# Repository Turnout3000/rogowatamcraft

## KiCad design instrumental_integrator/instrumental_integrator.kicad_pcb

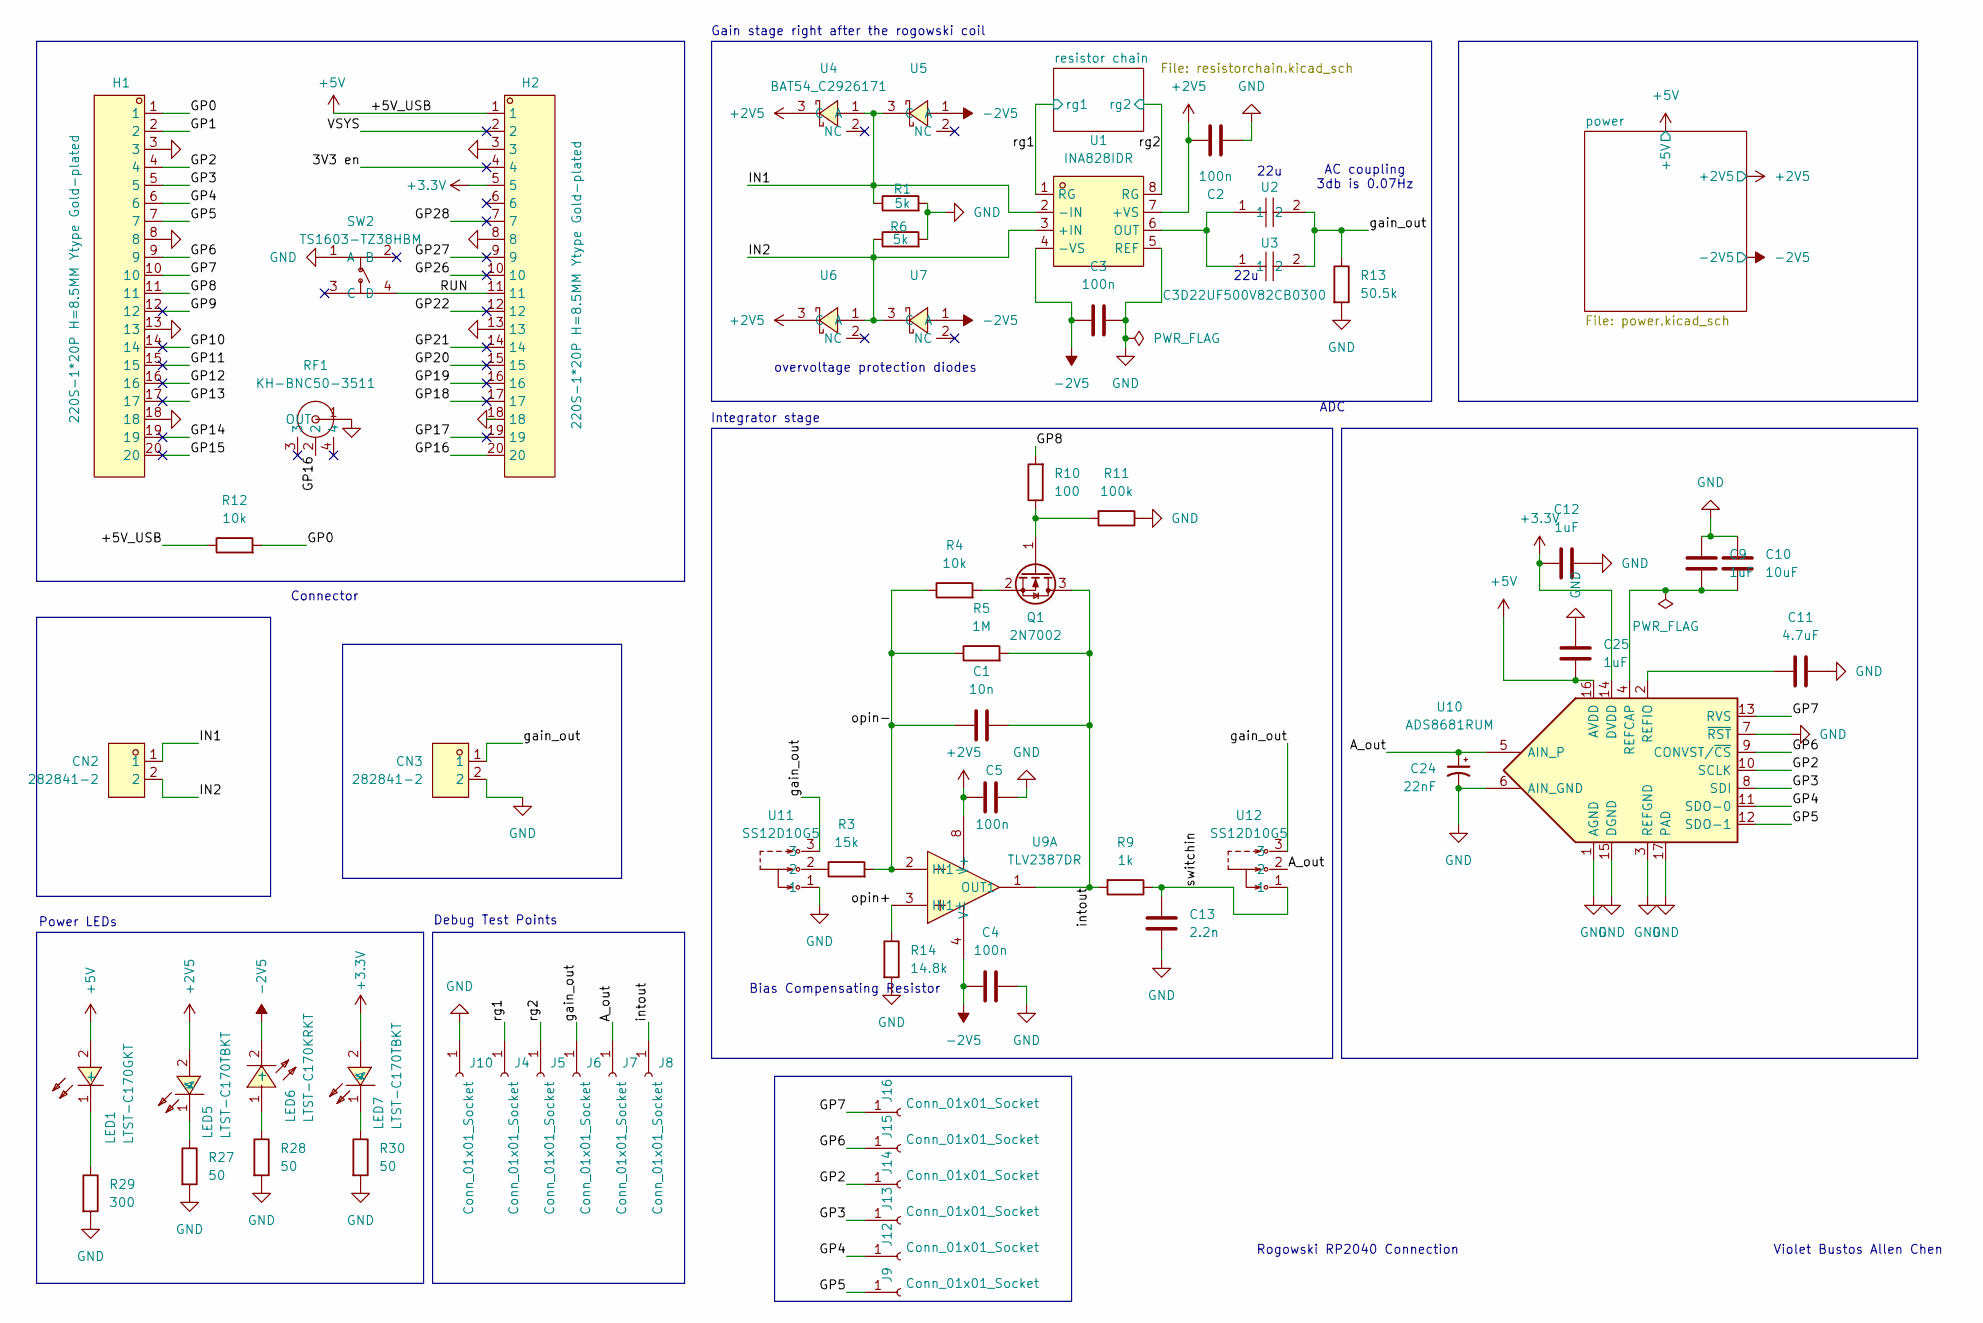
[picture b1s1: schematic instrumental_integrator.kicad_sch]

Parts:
C1: 10n; C_0603_1608Metric
C2, C3, C4, C5: 100n; C_0805_2012Metric
C9, C12, C25: 1uF; C_0603_1608Metric
C10: 10uF; C_0805_2012Metric
C11: 4.7uF; C_0805_2012Metric
C13: 2.2n; C_0805_2012Metric
C24: 22nF; C_1206_3216Metric
CN2, CN3: 282841-2; CONN-TH_2P-P5.08_282841-2; MPN 282841-2; LCSC Part C589673
H1, H2: 220S-1*20P H=8.5MM Ytype Gold-plated; HDR-TH_20P-P2.54-V-F; MPN B-2200S20P-A120; LCSC Part C124410
J4, J5, J6, J7, J8, J9, J10, J12, J13, J14, J15, J16: Conn_01x01_Socket; TestPoint_THTPad_1.0x1.0mm_Drill0.5mm
LED1: LTST-C170GKT; LED0805-RD_GREEN; MPN LTST-C170GKT; LCSC Part C125090
LED5, LED7: LTST-C170TBKT; LED0805-RD_BLUE; MPN LTST-C170TBKT; LCSC Part C98222
LED6: LTST-C170KRKT; LED0805-R-RD; MPN LTST-C170KRKT; LCSC Part C94868
Q1: 2N7002; SOT-23
R1, R6: 5k; R_0805_2012Metric
R3: 15k; R_0805_2012Metric
R4, R12: 10k; R_0805_2012Metric
R5: 1M; R_0805_2012Metric
R9: 1k; R_0805_2012Metric
R10: 100; R_0805_2012Metric
R11: 100k; R_0805_2012Metric
R13: 50.5k; R_0805_2012Metric
R14: 14.8k; R_0805_2012Metric
R27, R28, R30: 50; R_0805_2012Metric
R29: 300; R_0805_2012Metric
RF1: KH-BNC50-3511; ANT-TH_KH-BNC50-3511; MPN KH-BNC50-3511; LCSC Part C2837587
SW2: TS1603-TZ38HBM; SW-SMD_4P-L4.5-W4.5-P3.00-LS6.8; MPN TS1603-TZ38HBM; LCSC Part C36938886
U1: INA828IDR; SOIC-8_L4.9-W3.9-P1.27-LS6.0-BL; MPN INA828IDR; LCSC Part C544342
U2, U3: C3D22UF500V82CB0300; CAP-TH_L32.0-W22.0-P27.50-D1.3; MPN C3D22UF500V82CB0300; LCSC Part C5263851
U4, U5, U6, U7: BAT54_C2926171; SOT-23-3_L2.9-W1.3-P0.95-LS2.4-BR; MPN BAT54; LCSC Part C2926171
U9: TLV2387DR; SOIC-8_L4.9-W3.9-P1.27-LS6.2-BL; MPN TLV2387DR; LCSC Part C22445452
U10: ADS8681RUM; QFN-16-1EP_4x4mm_P0.65mm_EP2.7x2.7mm
U11, U12: SS12D10G5; SW-TH_SHOU-HAN_SS12D10G4; MPN SS12D10G5; LCSC Part C7431054

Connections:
+2V5: C2.1, C5.1, LED5.2 (A), U1.7 (+VS), U4.3 (C), U6.3 (C), U9.8 (V+); also elsewhere on the board
+3.3V: C12.1, H2.5, LED7.2 (A), U10.14 (DVDD)
+5V: C25.1, H2.1, LED1.2 (+), R12.1, U10.16 (AVDD); also elsewhere on the board
-2V5: C3.2, C4.1, LED6.2 (-), U1.4 (-VS), U5.1 (A), U7.1 (A), U9.4 (V-); also elsewhere on the board
/3V3 en: H2.4
/A_out: C24.1, J7.1 (Pin_1_1), U10.5 (AIN_P), U12.2
/GP0: H1.1, R12.2
/GP1: H1.2
/GP2: H1.4, J14.1 (Pin_1_1), U10.10 (SCLK)
/GP3: H1.5, J13.1 (Pin_1_1), U10.8 (SDI)
/GP4: H1.6, J12.1 (Pin_1_1), U10.11 (SDO-0)
/GP5: H1.7, J9.1 (Pin_1_1), U10.12 (SDO-1)
/GP6: H1.9, J15.1 (Pin_1_1), U10.9 (CONVST/~CS)
/GP7: H1.10, J16.1 (Pin_1_1), U10.13 (RVS)
/GP8: H1.11, R10.2
/GP9: H1.12
/GP10: H1.14
/GP11: H1.15
/GP12: H1.16
/GP13: H1.17
/GP14: H1.19
/GP15: H1.20
/GP16: H2.20, RF1.2
/GP17: H2.19
/GP18: H2.17
/GP19: H2.16
/GP20: H2.15
/GP21: H2.14
/GP22: H2.12
/GP26: H2.10
/GP27: H2.9
/GP28: H2.7
/IN1: CN2.1, R1.1, U1.2 (-IN), U4.1 (A), U5.3 (C)
/IN2: CN2.2, R6.1, U1.3 (+IN), U6.1 (A), U7.3 (C)
/RUN: H2.11, SW2.4 (D)
/VSYS: H2.2
/gain_out: CN3.1, J6.1 (Pin_1_1), R13.1, U2.2, U3.2, U11.3, U12.3
/intout: C1.2, J8.1 (Pin_1_1), Q1.3 (D), R5.2, R9.2, U9.1 (OUT1)
/opin+: R14.1, U9.3 (IN1+)
/opin-: C1.1, R3.2, R4.1, R5.1, U9.2 (IN1-)
/rg1: J4.1 (Pin_1_1), U1.1 (RG); also elsewhere on the board
/rg2: J5.1 (Pin_1_1), U1.8 (RG); also elsewhere on the board
/switchin: C13.1, R9.1, U12.1
GND: C2.2, C3.1, C4.2, C5.2, C9.1, C10.1, C11.2, C12.2, C13.2, C24.2, C25.2, CN3.2, H1.3, H1.8, H1.13, H1.18, H2.3, H2.8, H2.13, H2.18, J10.1 (Pin_1_1), R1.2, R6.2, R11.1, R13.2, R14.2, R27.2, R28.2, R29.2, R30.2, RF1.1 (OUT), SW2.1 (A), U1.5 (REF), U10.1 (AGND), U10.3 (REFGND), U10.6 (AIN_GND), U10.7 (~RST), U10.15 (DGND), U10.17 (PAD), U11.1; also elsewhere on the board
unnamed: LED1.1 (-), R29.1
unnamed: LED5.1 (K), R27.1
unnamed: LED6.1 (+), R28.1
unnamed: LED7.1 (K), R30.1
unnamed: Q1.1 (G), R10.1, R11.2
unnamed: Q1.2 (S), R4.2
unnamed: R3.1, U11.2
unnamed: U1.6 (OUT), U2.1, U3.1
unnamed: C9.2, C10.2, U10.4 (REFCAP)
unnamed: C11.1, U10.2 (REFIO)

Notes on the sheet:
Gain stage right after the rogowski coil
Debug Test Points
ADC
Rogowski RP2040 Connection
22u
Power LEDs
Violet Bustos Allen Chen
Bias Compensating Resistor
AC coupling 3db is 0.07Hz
overvoltage protection diodes
Connector
Integrator stage

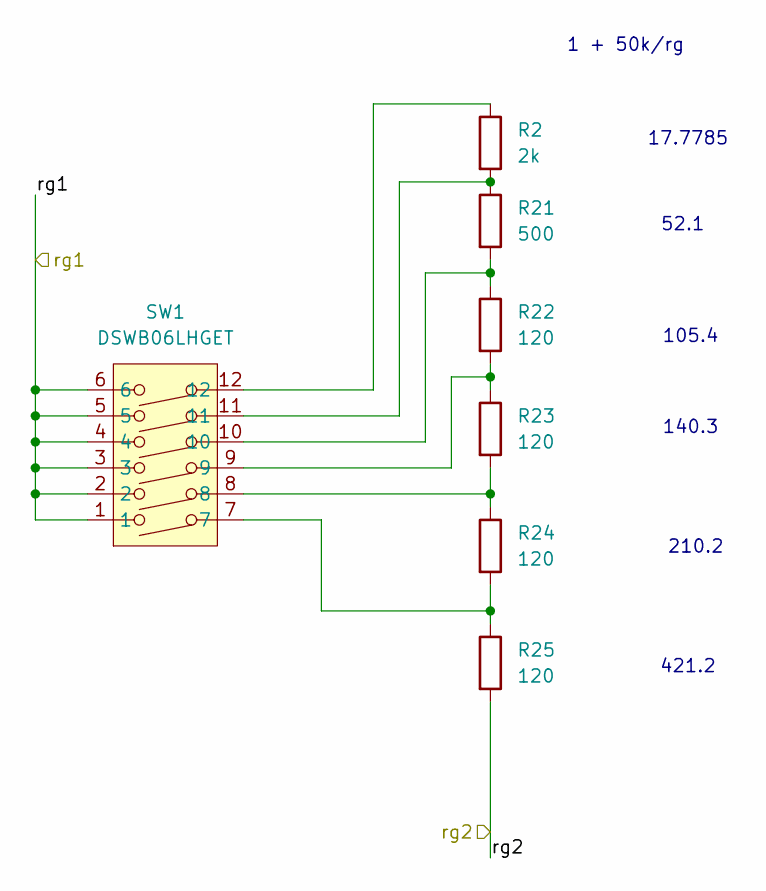
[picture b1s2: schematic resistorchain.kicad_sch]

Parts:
R2: 2k; R_0805_2012Metric
R21: 500; R_0805_2012Metric
R22, R23, R24, R25: 120; R_0805_2012Metric
SW1: DSWB06LHGET; SW-TH_DSWB06LHGET; MPN DSWB06LHGET; LCSC Part C99416

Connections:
/rg1: SW1.1, SW1.2, SW1.3, SW1.4, SW1.5, SW1.6; also elsewhere on the board
/rg2: R25.2; also elsewhere on the board
unnamed: R2.1, SW1.12
unnamed: R2.2, R21.1, SW1.11
unnamed: R21.2, R22.1, SW1.10
unnamed: R22.2, R23.1, SW1.9
unnamed: R23.2, R24.1, SW1.8
unnamed: R24.2, R25.1, SW1.7

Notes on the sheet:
1 + 50k/rg
140.3
210.2
17.7785
421.2
105.4
52.1

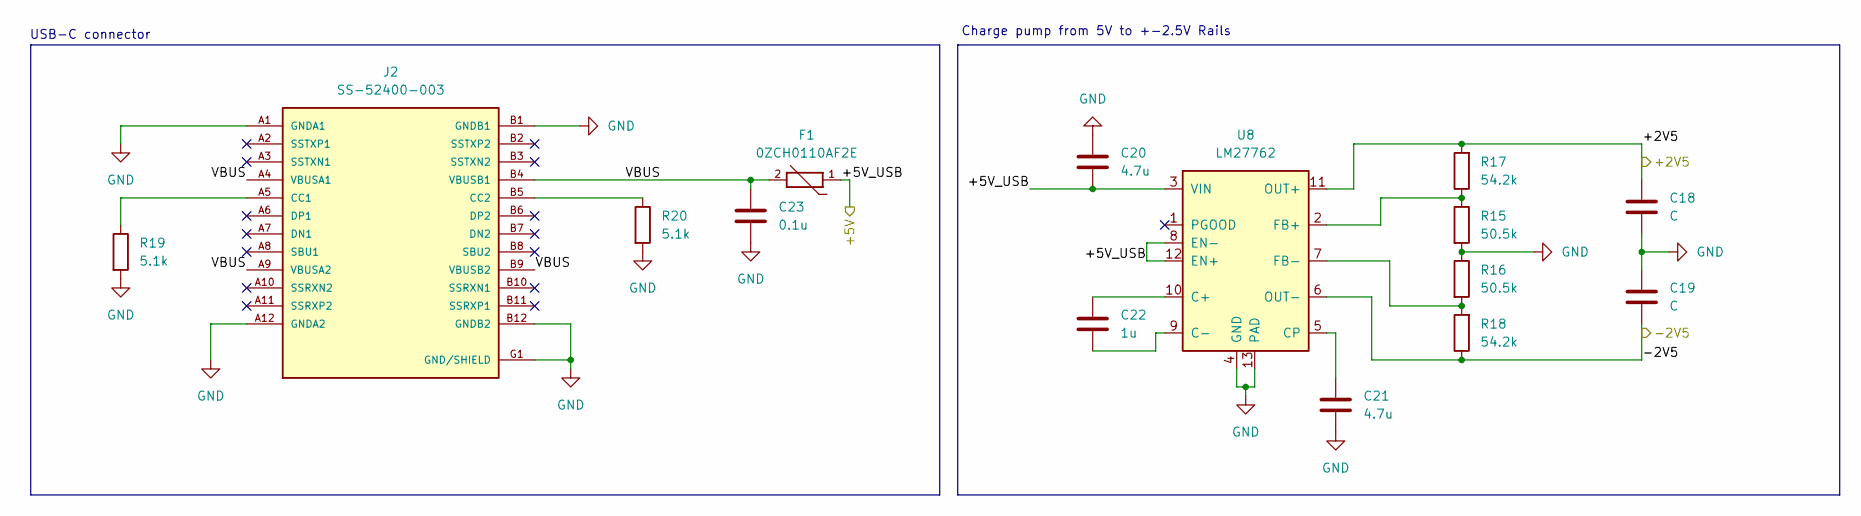
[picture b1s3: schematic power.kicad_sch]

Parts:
C18, C19: C
C20, C21: 4.7u
C22: 1u
C23: 0.1u
F1: 0ZCH0110AF2E; FUSC3225X100N; PARTREV Apr2023; DigiKey_Part_Number 5923-0ZCH0110AF2ECT-ND
J2: SS-52400-003; BELFUSE_SS-52400-003; PARTREV A0; DigiKey_Part_Number 380-SS-52400-003CT-ND
R15, R16: 50.5k
R17, R18: 54.2k
R19, R20: 5.1k
U8: LM27762; WSON-12-1EP_3x2mm_P0.5mm_EP1x2.65_ThermalVias

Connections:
+2V5: C18.1, R17.2, U8.11 (OUT+); also elsewhere on the board
+5V: C20.2, F1.1, U8.3 (VIN), U8.8 (EN-), U8.12 (EN+); also elsewhere on the board
-2V5: C19.2, R18.1, U8.6 (OUT-); also elsewhere on the board
/power/VBUS: C23.1, F1.2, J2.A4 (VBUSA1), J2.A9 (VBUSA2), J2.B4 (VBUSB1), J2.B9 (VBUSB2); also elsewhere on the board
GND: C18.2, C19.1, C20.1, C21.2, C23.2, J2.A1 (GNDA1), J2.A12 (GNDA2), J2.B1 (GNDB1), J2.B12 (GNDB2), J2.G1 (GND/SHIELD), J2.G2 (GND/SHIELD), J2.G3 (GND/SHIELD), J2.G4 (GND/SHIELD), J2.S1 (GND/SHIELD), J2.S2 (GND/SHIELD), J2.S3 (GND/SHIELD), J2.S4 (GND/SHIELD), R15.2, R16.1, R19.2, R20.2, U8.4 (GND), U8.13 (PAD); also elsewhere on the board
unnamed: J2.A5 (CC1), R19.1
unnamed: J2.B5 (CC2), R20.1
unnamed: C22.1, U8.10 (C+)
unnamed: C22.2, U8.9 (C-)
unnamed: C21.1, U8.5 (CP)
unnamed: R15.1, R17.1, U8.2 (FB+)
unnamed: R16.2, R18.2, U8.7 (FB-)

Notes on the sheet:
Charge pump from 5V to +-2.5V Rails
USB-C connector

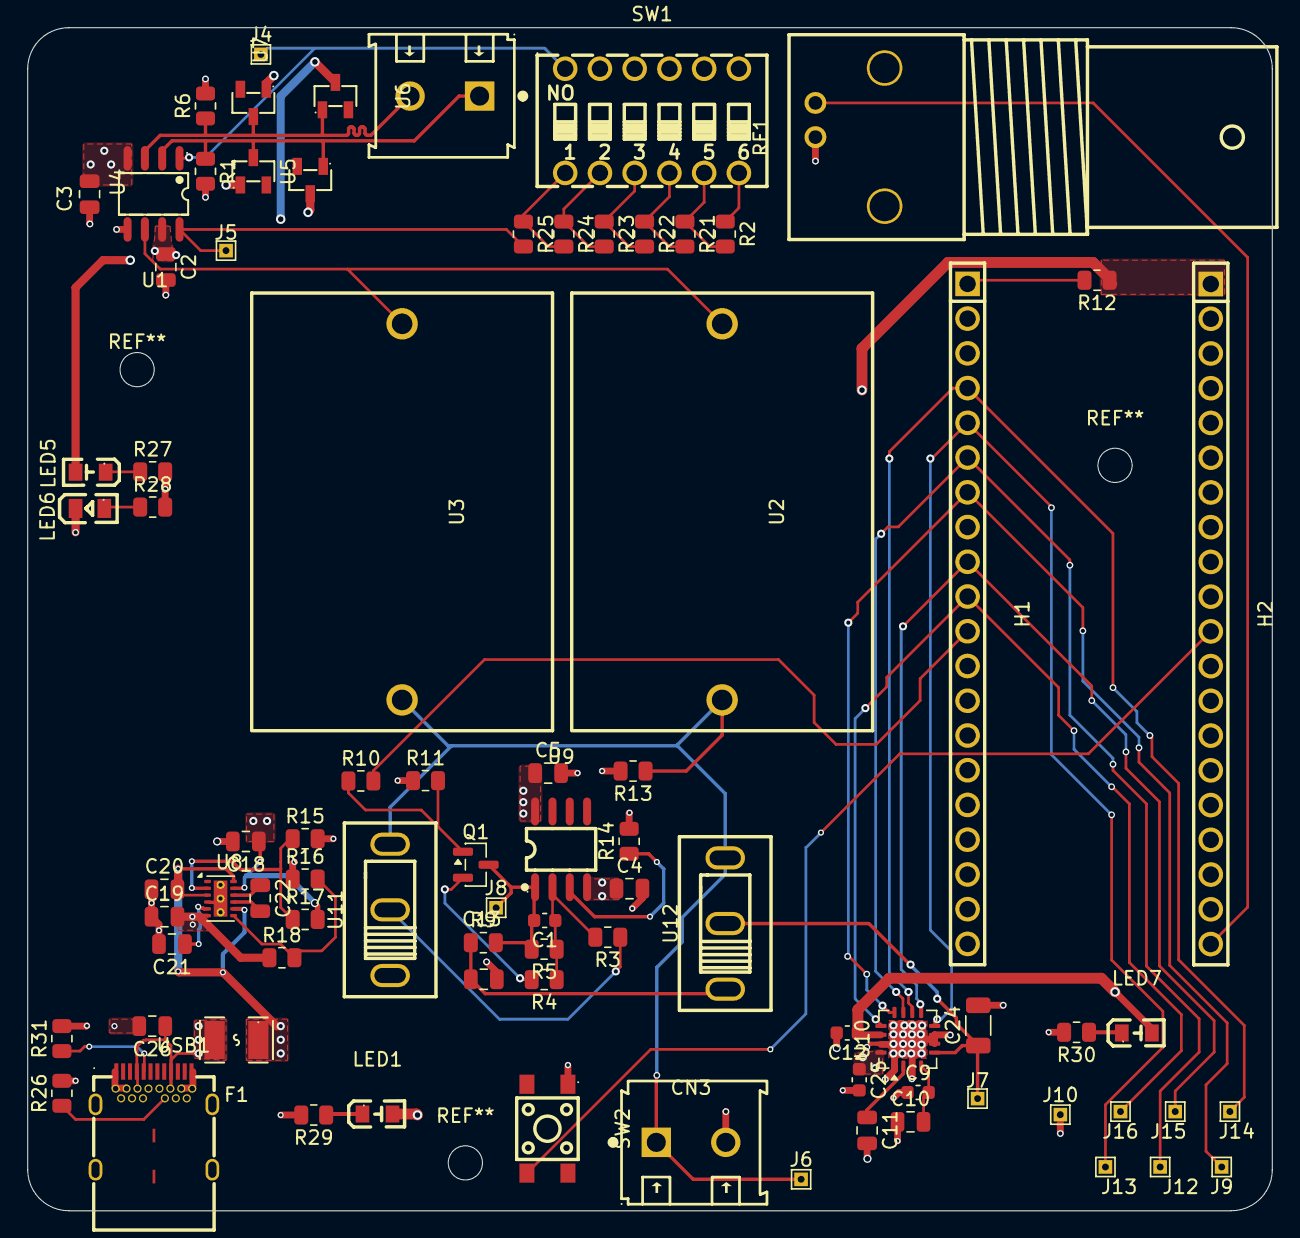
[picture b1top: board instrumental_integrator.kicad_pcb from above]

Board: 4 copper layers, 91.0 x 86.5 mm, 83 parts (0 on the bottom side), 49 nets.

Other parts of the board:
C26: 0.1u; C_0805_2012Metric
R26, R31: 5.1k; R_0805_2012Metric
USB1: SS-52400-003; TYPE-C-SMD_SS-52400-003

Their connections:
/power/VBUS: C26.1, USB1.A4 (VBUS), USB1.A9 (VBUS), USB1.B4 (VBUS), USB1.B9 (VBUS); also elsewhere on the board
GND: C26.2, R26.2, R31.2, USB1.A1 (GND), USB1.A12 (GND), USB1.B1 (GND), USB1.B12 (GND), USB1.GND; also elsewhere on the board
unnamed: R31.1, USB1.A5 (CC1)
unnamed: R26.1, USB1.B5 (CC2)
